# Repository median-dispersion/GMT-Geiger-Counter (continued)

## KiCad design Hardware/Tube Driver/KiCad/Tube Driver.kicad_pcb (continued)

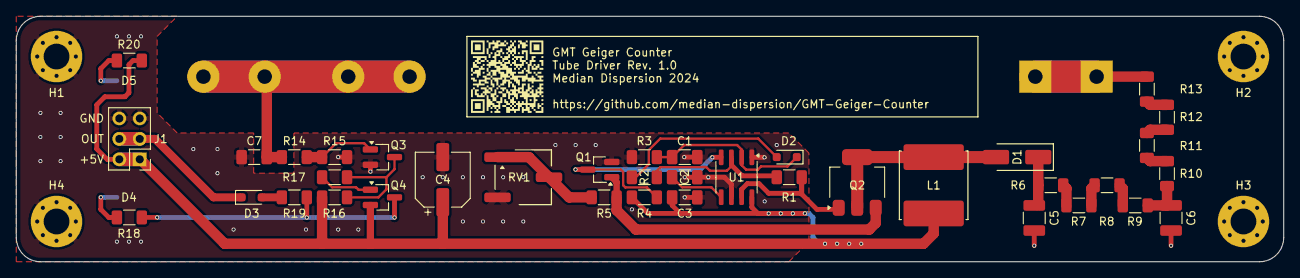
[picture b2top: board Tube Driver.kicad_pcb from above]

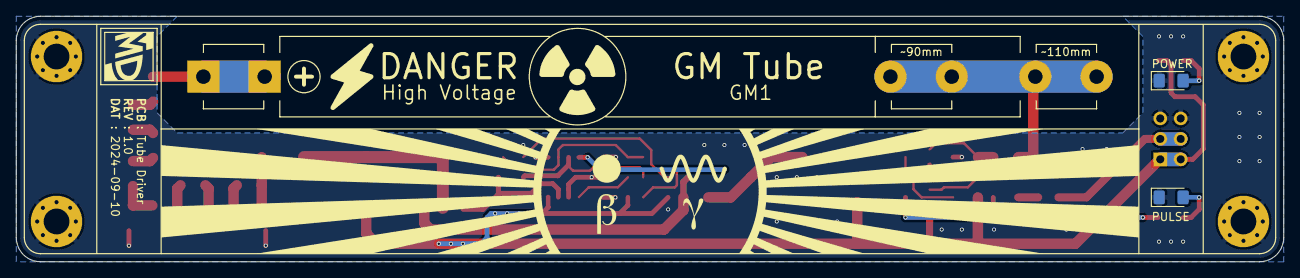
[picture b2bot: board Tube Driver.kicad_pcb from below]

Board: 2 copper layers, 157.5 x 30.5 mm, 45 parts (3 on the bottom side), 29 nets.

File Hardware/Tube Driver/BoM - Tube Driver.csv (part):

"Reference","Value","Qty","Footprint","MPN","Datasheet","DigiKey","Price (EUR)"
"C1","1nF","1","Capacitor_SMD:C_1206_3216Metric_Pad1.33x1.80mm_HandSolder","885012208046","https://www.we-online.com/components/products/datasheet/8850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","https://www.digikey.com/en/products/detail/w%C3%BCrth-elektr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","0,09€"
"C2","10nF","1","Capacitor_SMD:C_1206_3216Metric_Pad1.33x1.80mm_HandSolder","885012208112","https://www.we-online.com/components/products/datasheet/8850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","https://www.digikey.com/en/products/detail/w%C3%BCrth-elektr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","0,1€"
"C3","10nF","1","Capacitor_SMD:C_1206_3216Metric_Pad1.33x1.80mm_HandSolder","885012208112","https://www.we-online.com/components/products/datasheet/8850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","https://www.digikey.com/en/products/detail/w%C3%BCrth-elektr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","0,1€"
"C4","100uF","1","Capacitor_SMD:CP_Elec_6.3x5.4","865080243007","https://www.we-online.com/components/products/datasheet/8650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","https://www.digikey.com/en/products/detail/w%C3%BCrth-elektr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","0,25€"
"C5","47pF","1","Capacitor_SMD:C_1210_3225Metric_Pad1.33x2.70mm_HandSolder","C1210V473KDRAC7800","https://search.kemet.com/download/datasheet/C1210V473KDRAC7800","https://www.digikey.com/en/products/detail/kemet/C1210V473KD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","0,31€"
"C6","47pF","1","Capacitor_SMD:C_1210_3225Metric_Pad1.33x2.70mm_HandSolder","C1210V473KDRAC7800","https://search.kemet.com/download/datasheet/C1210V473KDRAC7800","https://www.digikey.com/en/products/detail/kemet/C1210V473KD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","0,31€"
"C7","820pF","1","Capacitor_SMD:C_1206_3216Metric_Pad1.33x1.80mm_HandSolder","CC1206FRNPO9BN821","https://www.yageo.com/upload/media/product/productsearch/dat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","https://www.digikey.com/en/products/detail/yageo/CC1206FRNPO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","0,45€"
"D1","RS1J","1","Footprints:D_SMA_HV_Handsoldering","RS1J-13-F","https://www.diodes.com/assets/Datasheets/ds15002.pdf","https://www.digikey.com/en/products/detail/diodes-incorporat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","0,4€"
"D2","1N914BWS","1","Diode_SMD:D_SOD-323_HandSoldering","1N914BWS","https://rocelec.widen.net/view/pdf/tf3dlteblx/FAIR-S-A000057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","https://www.digikey.com/en/products/detail/onsemi/1N914BWS/1873807","0,14€"
"D3","RB751V-40","1","Diode_SMD:D_SOD-323_HandSoldering","RB751V-40_R1_00001","https://www.panjit.com.tw/upload/datasheet/RB751V-40.pdf","https://www.digikey.com/en/products/detail/panjit-internatio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","0,14€"
"D4","GREEN","1","LED_SMD:LED_1206_3216Metric_Pad1.42x1.75mm_HandSolder","150120GS75000","https://www.we-online.com/components/products/datasheet/1501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","https://www.digikey.com/en/products/detail/w%C3%BCrth-elektr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","0,2€"
"D5","RED","1","LED_SMD:LED_1206_3216Metric_Pad1.42x1.75mm_HandSolder","150120RS75000","https://www.we-online.com/components/products/datasheet/1501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","https://www.digikey.com/en/products/detail/w%C3%BCrth-elektr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","0,2€"
"GM1","Geiger-Müller Tube","1","Footprints:GM_Tube_Mount","FC-102  BRIGHT TIN","https://www.belfuse.com/resources/datasheets/circuitprotecti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","https://www.digikey.com/en/products/detail/bel-fuse-inc/FC-1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","0,1€"
"J1","I/O","1","Connector_PinHeader_2.54mm:PinHeader_2x03_P2.54mm_Vertical","PH2-06-UA","https://app.adam-tech.com/products/download/data_sheet/20206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","https://www.digikey.com/en/products/detail/adam-tech/PH2-06-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","0,11€"
"L1","10mH","1","Footprints:L_8065_HandSolder","74404086103","https://www.we-online.com/components/products/datasheet/7440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","https://www.digikey.com/en/products/detail/w%C3%BCrth-elektr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","1,13€"
"Q1","MMBT3904","1","Package_TO_SOT_SMD:SOT-23_Handsoldering","MMBT3904","https://goodarksemi.com/docs/datasheets/transistors/MMBT3904.pdf","https://www.digikey.com/en/products/detail/good-ark-semicond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","0,09€"
"Q2","STN2580","1","Package_TO_SOT_SMD:SOT-223","STN2580","https://www.st.com/content/ccc/resource/technical/document/d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","https://www.digikey.com/en/products/detail/stmicroelectronic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","0,48€"
"Q3","MMBT3904","1","Package_TO_SOT_SMD:SOT-23_Handsoldering","MMBT3904","https://goodarksemi.com/docs/datasheets/transistors/MMBT3904.pdf","https://www.digikey.com/en/products/detail/good-ark-semicond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","0,09€"
"Q4","MMBT3906","1","Package_TO_SOT_SMD:SOT-23_Handsoldering","MMBT3906","https://goodarksemi.com/docs/datasheets/transistors/MMBT3906.pdf","https://www.digikey.com/en/products/detail/good-ark-semicond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","0,09€"
"R1","330","1","Resistor_SMD:R_1206_3216Metric_Pad1.30x1.75mm_HandSolder","RC1206FR-07330RL","https://www.yageo.com/upload/media/product/products/datashee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","https://www.digikey.com/en/products/detail/yageo/RC1206FR-07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","0,09€"
"R2","1k","1","Resistor_SMD:R_1206_3216Metric_Pad1.30x1.75mm_HandSolder","RC1206FR-071KL","https://www.yageo.com/upload/media/product/products/datashee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","https://www.digikey.com/en/products/detail/yageo/RC1206FR-07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","0,09€"
"R3","220k","1","Resistor_SMD:R_1206_3216Metric_Pad1.30x1.75mm_HandSolder","RC1206FR-07220KL","https://www.yageo.com/upload/media/product/products/datashee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","https://www.digikey.com/en/products/detail/yageo/RC1206FR-07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","0,09€"
"R4","100k","1","Resistor_SMD:R_1206_3216Metric_Pad1.30x1.75mm_HandSolder","AC1206FR-07100KL","https://www.yageo.com/upload/media/product/productsearch/dat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","https://www.digikey.com/en/products/detail/yageo/AC1206FR-07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","0,09€"
"R5","15","1","Resistor_SMD:R_1206_3216Metric_Pad1.30x1.75mm_HandSolder","RC1206FR-0715RL","https://www.yageo.com/upload/media/product/products/datashee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","https://www.digikey.com/en/products/detail/yageo/RC1206FR-07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","0,09€"
"R6","240k","1","Resistor_SMD:R_1206_3216Metric_Pad1.30x1.75mm_HandSolder","RC1206FR-07240KL","https://www.yageo.com/upload/media/product/products/datashee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","https://www.digikey.com/en/products/detail/yageo/RC1206FR-07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","0,09€"
"R7","240k","1","Resistor_SMD:R_1206_3216Metric_Pad1.30x1.75mm_HandSolder","RC1206FR-07240KL","https://www.yageo.com/upload/media/product/products/datashee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","https://www.digikey.com/en/products/detail/yageo/RC1206FR-07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","0,09€"
"R8","240k","1","Resistor_SMD:R_1206_3216Metric_Pad1.30x1.75mm_HandSolder","RC1206FR-07240KL","https://www.yageo.com/upload/media/product/products/datashee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","https://www.digikey.com/en/products/detail/yageo/RC1206FR-07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","0,09€"
"R9","240k","1","Resistor_SMD:R_1206_3216Metric_Pad1.30x1.75mm_HandSolder","RC1206FR-07240KL","https://www.yageo.com/upload/media/product/products/datashee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","https://www.digikey.com/en/products/detail/yageo/RC1206FR-07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","0,09€"
"R10","1.2M","1","Resistor_SMD:R_1206_3216Metric_Pad1.30x1.75mm_HandSolder","RC1206FR-071M2L","https://www.yageo.com/upload/media/product/products/datashee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","https://www.digikey.com/en/products/detail/yageo/RC1206FR-07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","0,09€"
"R11","1.2M","1","Resistor_SMD:R_1206_3216Metric_Pad1.30x1.75mm_HandSolder","RC1206FR-071M2L","https://www.yageo.com/upload/media/product/products/datashee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","https://www.digikey.com/en/products/detail/yageo/RC1206FR-07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","0,09€"
"R12","1.2M","1","Resistor_SMD:R_1206_3216Metric_Pad1.30x1.75mm_HandSolder","RC1206FR-071M2L","https://www.yageo.com/upload/media/product/products/datashee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","https://www.digikey.com/en/products/detail/yageo/RC1206FR-07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","0,09€"
"R13","1.2M","1","Resistor_SMD:R_1206_3216Metric_Pad1.30x1.75mm_HandSolder","RC1206FR-071M2L","https://www.yageo.com/upload/media/product/products/datashee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","https://www.digikey.com/en/products/detail/yageo/RC1206FR-07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","0,09€"
"R14","22k","1","Resistor_SMD:R_1206_3216Metric_Pad1.30x1.75mm_HandSolder","RC1206FR-0722KL","https://www.yageo.com/upload/media/product/products/datashee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","https://www.digikey.com/en/products/detail/yageo/RC1206FR-07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","0,09€"
"R15","22k","1","Resistor_SMD:R_1206_3216Metric_Pad1.30x1.75mm_HandSolder","RC1206FR-0722KL","https://www.yageo.com/upload/media/product/products/datashee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","https://www.digikey.com/en/products/detail/yageo/RC1206FR-07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","0,09€"
"R16","10k","1","Resistor_SMD:R_1206_3216Metric_Pad1.30x1.75mm_HandSolder","RC1206FR-1310KL","https://www.yageo.com/upload/media/product/products/datashee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","https://www.digikey.com/en/products/detail/yageo/RC1206FR-13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","0,09€"
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
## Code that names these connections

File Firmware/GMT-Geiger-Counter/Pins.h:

#ifndef PINS_H
#define PINS_H

#include "Arduino.h"
#include "Configuration.h"

void setupPins() {

    // Set pin modes
    // -------------

    // SPI Pins
    pinMode(DISPLAY_CS_PIN, OUTPUT);
    pinMode(TOUCH_CS_PIN, OUTPUT);
    pinMode(SD_CS_PIN, OUTPUT);
    pinMode(SCK_PIN, OUTPUT);
    pinMode(MOSI_PIN, OUTPUT);
    pinMode(MISO_PIN, INPUT);

    // Display pins
    pinMode(DISPLAY_LED_PIN, OUTPUT);
    pinMode(DISPLAY_RST_PIN, OUTPUT);
    pinMode(DISPLAY_DC_PIN, OUTPUT);

    // Touchscreen pins
    pinMode(TOUCH_IRQ_PIN, INPUT);

    // Tube pins
    pinMode(MAIN_TRG_PIN, INPUT);
    pinMode(FOLLOWER_TRG_PIN, INPUT);
    pinMode(COINCIDENCE_TRG_PIN, INPUT);

    // Other pins
    pinMode(BUZZER_PIN, OUTPUT);
    pinMode(RGB_LED_PIN, OUTPUT);

    // Set pin states
    // --------------

    // SPI Pins
    digitalWrite(DISPLAY_CS_PIN, HIGH);
    digitalWrite(TOUCH_CS_PIN, HIGH);
    digitalWrite(SD_CS_PIN, HIGH);
    digitalWrite(SCK_PIN, LOW);
    digitalWrite(MOSI_PIN, LOW);

    // Display pins
    digitalWrite(DISPLAY_LED_PIN, LOW);
    digitalWrite(DISPLAY_RST_PIN, HIGH);
    digitalWrite(DISPLAY_DC_PIN, HIGH);

    // Other pins
    pinMode(BUZZER_PIN, LOW);
    pinMode(RGB_LED_PIN, LOW);

}

#endif

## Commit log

2024-09-03 Added SPICE Simulations
2024-09-04 Tube Driver Rev. 1.0
2024-09-06 Added BoM, updated component values and PCB
2024-09-06 Added Gerber for manufacturing
2024-09-06 Fixed broken footprint
2024-09-06 Added symbols and footprints
2024-09-06 Added Motherboard schematic Rev. 1.0
2024-09-08 Motherboard PCB Rev. 1.0
2024-09-08 Cleaned up SVG files
2024-09-10 Added BoM for motherboard
2024-09-10 Fixed disconnected pad
2024-09-10 Added motherboard Gerber for manufacturing
2024-09-10 Fixed component value typo
2024-09-10 Updated Gerber
2024-09-10 Updated PCB screenshot
2024-09-18 Updated BoM
2024-09-22 Added firmware
2024-09-23 Updated firmware to display max and min pulse length
2024-10-03 Added Geiger counter class
2024-10-03 Added Buzzer class
2024-10-08 Added displays
2024-10-09 Updated displays
2024-10-17 Refactored Geiger counter class
2024-10-18 Added mobile case files
2024-10-18 Added tube driver model
2024-10-20 Added bottom case shell
2024-11-11 Added top case shell & support elements
2024-11-14 Changed component value, fixed typos & fixed small mistakes
2024-11-15 Fixed some things on the 3D model
2024-11-21 Added display layouts
2024-11-21 Updated display layouts
2025-01-15 Updated display graphics
2025-01-16 Added example screen
2025-01-17 Added display graphics
2025-01-17 Added additional display graphics
2025-01-25 Updated main firmware, adding touchscreen support
2025-01-27 Added display rotation functionality and cosmic ray detector screen
2025-01-27 Made screen setter functions more uniform
2025-01-29 Fixed type conversion and calculation issues
2025-01-29 Only draw new screen when display is set to on
2025-01-29 Added radiation history screen
2025-01-31 Updated radiation history screen
2025-02-03 Refactored main firmware to be less reliant on the String() implementation
2025-02-03 Added memory watchdog
2025-02-05 Added wireless interfaces
2025-02-12 Added bare-bones web interface and updated firmware so that the WiFi credentials can be changed via the web interface
2025-02-13 Added logger to main firmware
2025-02-13 Added screen update for elements that are changed programmatically instead of through user input
2025-02-13 Made WiFi connection non-blocking
2025-02-13 Fixed small issue with the logger class
2025-02-14 Added display auto timeout to the main firmware
2025-02-14 Added some README files
2025-02-15 Fixed smalls issues with the logger class
2025-02-15 Added a bunch of small memory optimizations to reduce RAM usage
2025-02-15 Added Geiger counter settings screens
2025-02-16 Added more measurement units and an auto range feature
2025-02-16 Fixed a small issue when alerts were muted no other sound would play
2025-02-16 Made WiFi settings persistent between reboots by storing them in the non-volatile memory
2025-02-27 Refactored main firmware and updated UI
2025-03-03 Updated 3D case model
2025-03-04 Added basic multi-language support to the webapp
2025-03-07 Updated .gitignore
2025-03-13 Added radiation rating and updated logging
2025-03-14 Added basic Geiger counter web app layout
2025-03-18 Updated main Geiger counter web-app
2025-03-19 Updated Geiger counter web-app
2025-03-21 Added local settings storage to the web-app and changed some UI elements in the main firmware
2025-04-29 Added SD card wrapper and rewrote logger
2025-04-29 Refactored wireless interface
2025-04-29 Added persistent settings storage and logging functionality
2025-05-01 Refactored Geiger counter
2025-05-01 Refactored cosmic ray detector
2025-05-01 Refactored buzzer
2025-05-01 Added touchscreen files
2025-05-02 Reimplemented bare-bones touchscreen functionality
2025-05-02 Added screens
2025-05-04 Removed wireless for testing, reimplemented most functions and fixed a bunch of small things
2025-05-04 Added wireless features back
2025-05-04 Added system info feedback
2025-05-04 Added back additional files
2025-05-04 Visually changed some screen elements
2025-05-05 Added RGB LED
2025-05-08 Updated event logging
2025-05-09 Added log file parser
2025-05-09 Added wireless logger
2025-05-23 Added serial logger
2025-05-23 Updated wireless and serial loggers
2025-05-23 Updated the decoupling capacitor to make it more USB 'compliant'
2025-06-05 Refactored logger tools
2025-06-13 Removed old web-app files
2025-06-17 Added Geiger counter web app source files
2025-06-17 Added web app build tool
2025-06-17 Updated API endpoints
2025-06-17 Improved Geiger counter web app
2025-06-18 Added root and updated Geiger counter web app
2025-06-18 Added WiFi settings web app and fixed small bugs in the other web app components.
2025-06-21 Added cosmic ray detector web app
2025-06-21 Updated web app builder script
2025-06-24 Built web app files
2025-06-25 Added system info web app
2025-06-25 Updated firmware
2025-06-27 Added audio feedback to Geiger counter web app
2025-06-27 Added German translation to system info web app
2025-06-27 Added case stands
2025-06-29 Updated mobile case
2025-06-30 Fixed 3D model
2025-06-30 Added audio feedback to the cosmic ray detector web app
2025-08-03 Redesigned thinner case stands to use less filament
2025-08-03 Updated the WiFi interface to automatically reconnect on loss or timeout #6
2025-08-04 Fixed display timeout resetting user settings #7
2025-08-05 Added multi-tube daisy chain measurement support and fixed an additional bug with issue #7
2025-08-05 Updated touch icons and addes 3 system settings screen
2025-08-06 Added absorbed dose readout feature
2025-08-07 Small bug fixes
2025-08-07 Updated wireless interface
2025-08-10 Added true random number generator interface
2025-08-11 Minor bug fixes
2025-08-12 Updated API endpoints and data output
2025-08-22 Updated READMEs
2025-09-21 Reverted to the old coincidence tube logic (Issue #8) and made the history line thicker
2025-11-10 Added manual pin setup to prevent rare SPI bus conflicts
2025-11-20 Updated display cover
2025-11-22 Added case labels
